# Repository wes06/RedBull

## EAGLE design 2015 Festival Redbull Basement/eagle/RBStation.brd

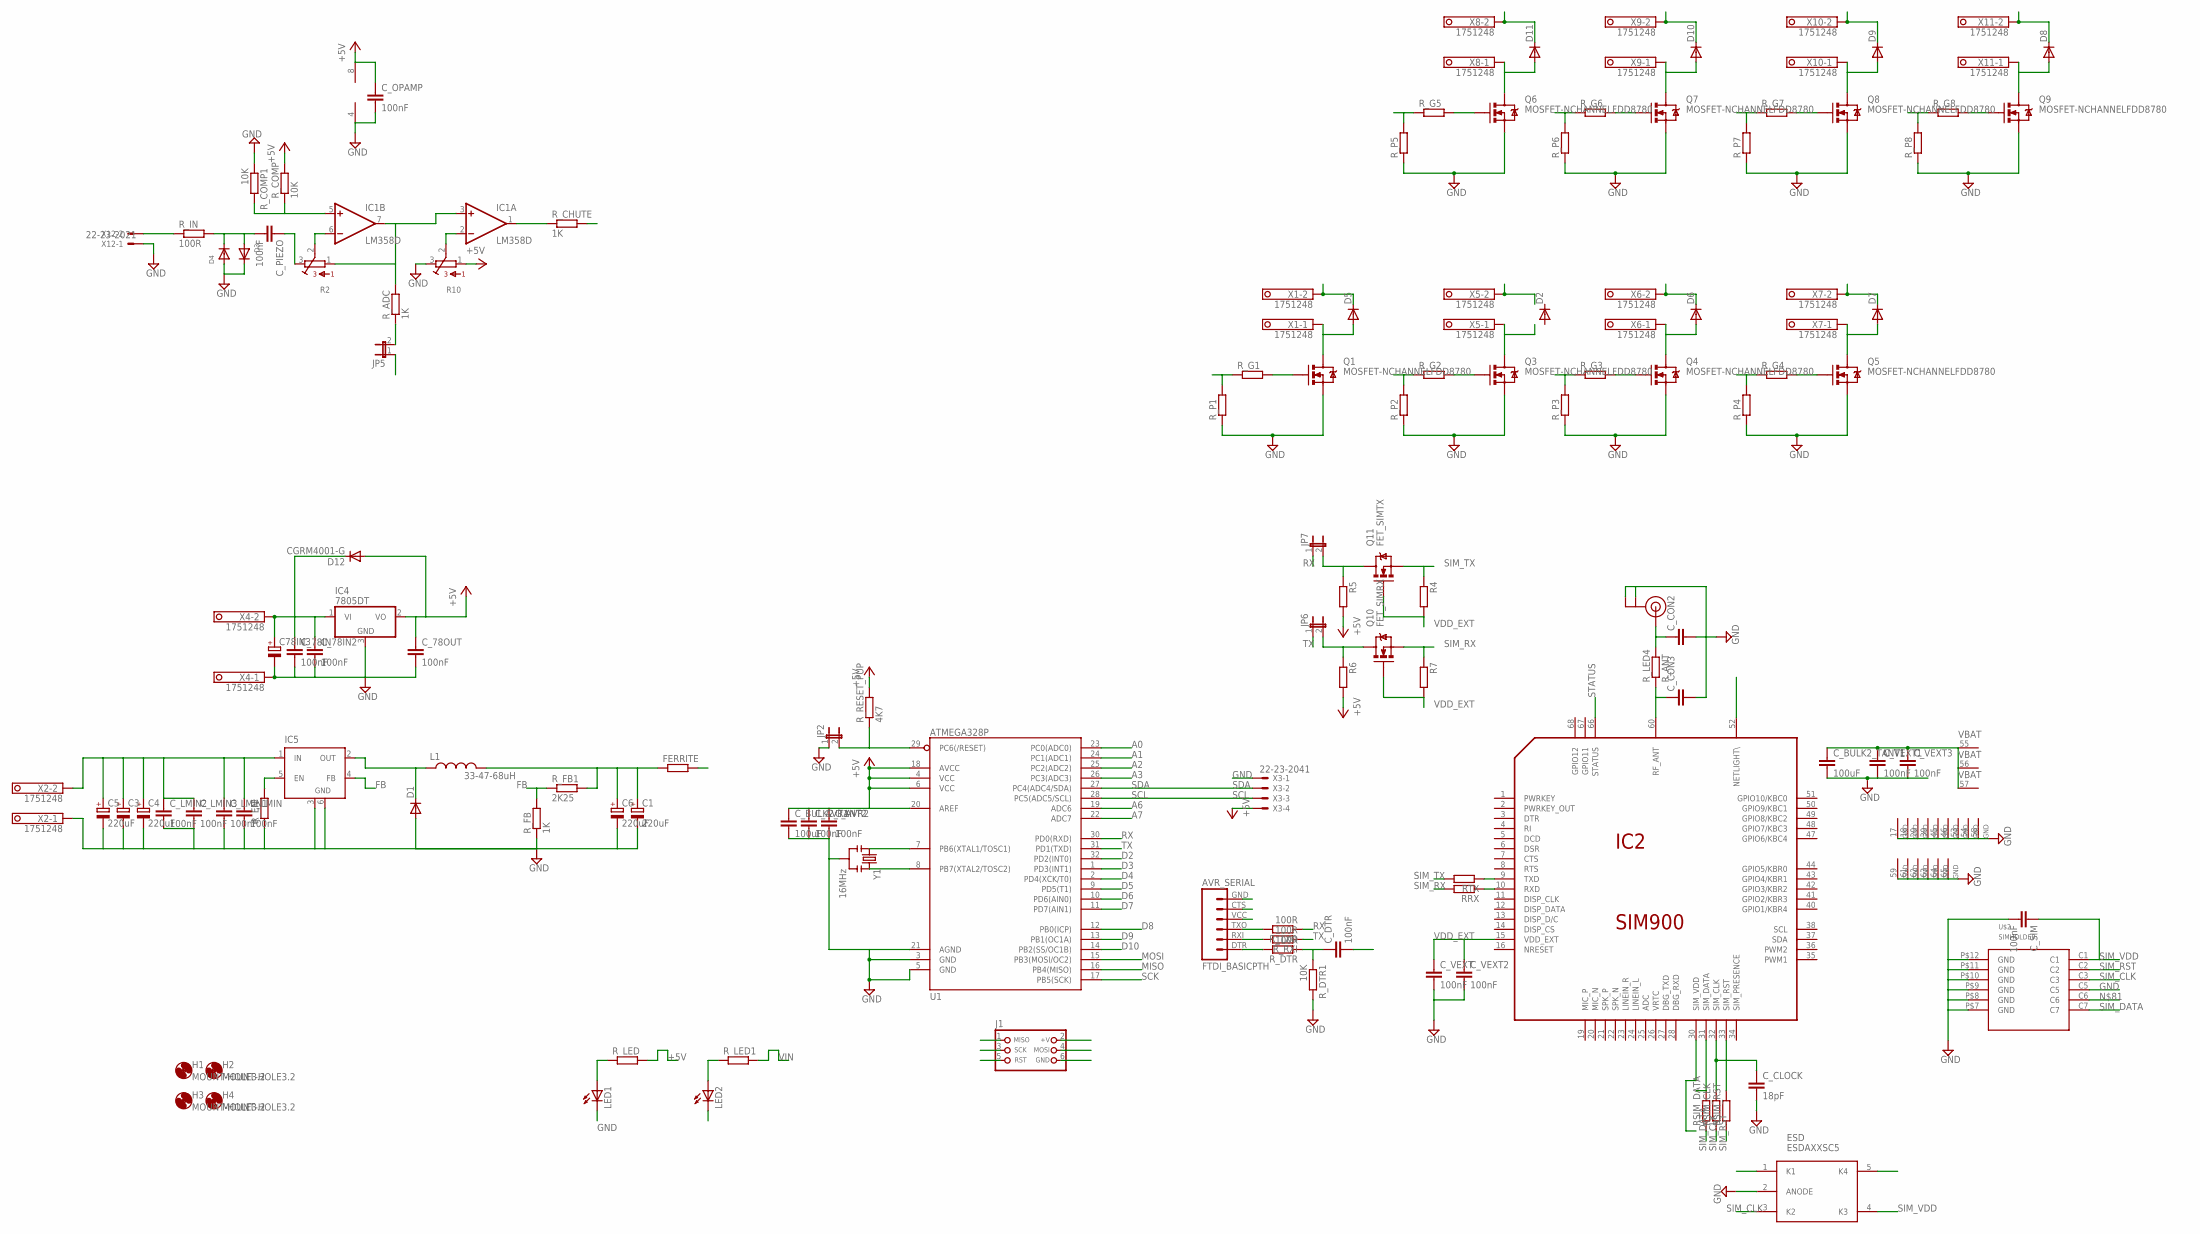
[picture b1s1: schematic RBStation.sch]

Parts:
AVR_SERIAL: FTDI_BASICPTH; FTDI_BASIC
C1, C4, C5, C6: 220uF; PANASONIC_F
C3, C78IN3: CPOL-EUF; PANASONIC_F
C_78IN, C_78IN2, C_78OUT: 100nF; C0805
C_AVR1: 100nF; C0805K
C_AVR2: 100nF; C0805
C_BULK2_TANT1, C_BULK2_TANT2: 100uF; C1210
C_CLOCK: 18pF; C0805
C_CON2, C_CON3: C-EUC0805; C0805
C_DTR: 100nF; C0805K
C_LMIN, C_LMIN1, C_LMIN2, C_LMIN3: 100nF; C0805
C_OPAMP: 100nF; C0805K
C_PIEZO: 100nF; C0805K
C_SIM: 100nF; C0805
C_VEXT, C_VEXT1, C_VEXT2: 100nF; C0805K
C_VEXT3: 100nF; C1210
D1: DIODESMB; SMB-DIODE
D2, D5, D6, D7, D8, D9, D10, D11: DIODESMA; SMA-DIODE
D3, D4: DIODESOD-123; SOD-123
D12: CGRM4001-G; SOD-123_MINI-SMA
ESD: ESDAXXSC5; SOT23-5
FERRITE: R-EU_R0805; R0805
H1, H2, H3, H4: MOUNT-HOLE3.2; 3,2
IC1: LM358D; SO08
IC2: SIM900
IC4: 7805DT; TO252
IC5: LM2596S; TO263-5
J1: CON_HEADER_PRG_AVR_ICSP; HEADER_PRG_2X03
JP2, JP5: JUMPER-2SMD-NC; SJ_2S
JP6, JP7: JUMPER-2PTH_LOCK; 1X02_LOCK
L1: 33-47-68uH; BOURNS-SRR1280
LED1, LED2: LEDCHIP-LED0805; CHIP-LED0805
Q1, Q3, Q4, Q5, Q6, Q7, Q8, Q9: MOSFET-NCHANNELFDD8780; DPAK
Q10: FET_SIMRX; SOT23
Q11: FET_SIMTX; SOT23
R2, R10: 3386-F; 3386F
R4, R5, R6, R7: R-EU_R0805; R0805
RRX: R-EU_M0805; M0805
RSIM_CLK: R-EU_M0805; M0805
RSIM_DATA: R-EU_M0805; M0805
RSIM_RST: R-EU_M0805; M0805
RTX: R-EU_M0805; M0805
R_ADC: 1K; M0805
R_CHUTE: 1K; M0805
R_COMP, R_COMP1: 10K; M0805
R_DTR: 100R; M0805
R_DTR1: 10K; M0805
R_EN: R-EU_M0805; M0805
R_FB: 1K; M0805
R_FB1: 2K25; M0805
R_G1, R_G2, R_G3, R_G4, R_G5, R_G6, R_G7, R_G8: R-EU_M0805; M0805
R_IN: 100R; M0805
R_LED, R_LED1: R-EU_M0805; M0805
R_LED4: R_ANT; R0805
R_P1, R_P2, R_P3, R_P4, R_P5, R_P6, R_P7, R_P8: R-EU_M0805; M0805
R_RESET_PUP: 4K7; M0805
R_RXI: 100R; M0805
R_TXO: 100R; M0805
U1: ATMEGA328P; TQFP32-08
U$1: U.FL
U$2: SIMHOLDER; WM9364CT-ND
X1, X2, X4, X5, X6, X7, X8, X9, X10, X11: 1751248
X3: 22-23-2041
X12: 22-23-2021
Y1: 16MHz; RESONATOR-SMD

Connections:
+5V: C_78OUT.1, C_AVR1.1, C_AVR2.1, C_BULK2_TANT2.1, C_OPAMP.1, D12.A, IC1.8 (V+), IC4.2 (VO), J1.2 (+V), R5.2, R6.2, R10.1, R_COMP.2, R_LED.2, R_RESET_PUP.2, U1.4 (VCC), U1.6 (VCC), U1.18 (AVCC), U1.20 (AREF), X3.4
A0: JP5.1, U1.23 (PC0(ADC0))
A1: U1.24 (PC1(ADC1))
A2: U1.25 (PC2(ADC2))
A3: U1.26 (PC3(ADC3))
A6: U1.19 (ADC6)
A7: U1.22 (ADC7)
C_CLK: C_CLOCK.1, IC2.32 (SIM_CLK), RSIM_CLK.2
D2: R_CHUTE.2, U1.32 (PD2(INT0))
D3: R_G1.1, R_P1.2, U1.1 (PD3(INT1))
D4: R_G2.1, R_P2.2, U1.2 (PD4(XCK/T0))
D5: R_G5.1, R_P5.2, U1.9 (PD5(T1))
D6: R_G6.1, R_P6.2, U1.10 (PD6(AIN0))
D7: R_G3.1, R_P3.2, U1.11 (PD7(AIN1))
D8: R_G4.1, R_P4.2, U1.12 (PB0(ICP))
D9: R_G7.1, R_P7.2, U1.13 (PB1(OC1A))
D10: R_G8.1, R_P8.2, U1.14 (PB2(SS/OC1B))
FB: IC5.4 (FB), R_FB.2, R_FB1.1
GND: AVR_SERIAL.GND (6), C1.-, C3.-, C4.-, C5.-, C6.-, C78IN3.-, C_78IN.2, C_78IN2.2, C_78OUT.2, C_AVR1.2, C_AVR2.2, C_BULK2_TANT1.2, C_BULK2_TANT2.2, C_CLOCK.2, C_CON2.2, C_CON3.2, C_LMIN.2, C_LMIN1.2, C_LMIN2.2, C_LMIN3.2, C_OPAMP.2, C_SIM.2, C_VEXT.2, C_VEXT1.2, C_VEXT2.2, C_VEXT3.2, D1.A, D3.C, D4.A, ESD.2 (ANODE), IC1.4 (V-), IC2.17 (GND), IC2.18 (GND), IC2.29 (GND), IC2.39 (GND), IC2.45 (GND), IC2.46 (GND), IC2.53 (GND), IC2.54 (GND), IC2.58 (GND), IC2.59 (GND), IC2.61 (GND), IC2.62 (GND), IC2.63 (GND), IC2.64 (GND), IC2.65 (GND), IC4.3 (GND), IC5.3 (GND), IC5.6 (GND), J1.6 (GND), JP2.1, LED1.C, LED2.C, Q1.3 (S), Q3.3 (S), Q4.3 (S), Q5.3 (S), Q6.3 (S), Q7.3 (S), Q8.3 (S), Q9.3 (S), R10.3, R_COMP1.1, R_DTR1.2, R_EN.1, R_FB.1, R_P1.1, R_P2.1, R_P3.1, R_P4.1, R_P5.1, R_P6.1, R_P7.1, R_P8.1, U1.3 (GND), U1.5 (GND), U1.21 (AGND), U$2.C5, U$2.P$7 (GND), U$2.P$8 (GND), U$2.P$9 (GND), U$2.P$10 (GND), U$2.P$11 (GND), U$2.P$12 (GND), X2.1, X3.1, X4.1, X12.1, Y1.2
MISO: J1.1 (MISO), U1.16 (PB4(MISO))
MOSI: J1.4 (MOSI), U1.15 (PB3(MOSI/OC2))
unnamed: Q1.1 (G), R_G1.2
unnamed: D1.C, IC5.2 (OUT), L1.P$2 (2)
unnamed: C_PIEZO.1, R2.3
unnamed: D5.A, Q1.4 (D), X1.1
unnamed: U1.7 (PB6(XTAL1/TOSC1)), Y1.1
unnamed: C_CON2.1, R_LED4.2, U$1.P$3 (SIGNAL)
unnamed: C_CON3.1, IC2.60 (RF_ANT), R_LED4.1
unnamed: IC2.31 (SIM_DATA), RSIM_DATA.2
unnamed: U$1.P$1 (GND), U$1.P$2 (GND)
unnamed: R_IN.1, X12.2
unnamed: U1.8 (PB7(XTAL2/TOSC2)), Y1.3
unnamed: IC2.33 (SIM_RST), RSIM_RST.2
unnamed: IC1.6 (-IN), R2.2
unnamed: JP5.2, R_ADC.1
unnamed: IC1.2 (-IN), R10.2
unnamed: C_BULK2_TANT1.1, C_VEXT1.1, C_VEXT3.1, FERRITE.2, IC2.55 (VBAT), IC2.56 (VBAT), IC2.57 (VBAT)
unnamed: LED2.A, R_LED1.1
unnamed: C_PIEZO.2, D3.A, D4.C, R_IN.2
unnamed: IC1.3 (+IN), IC1.7 (OUT), R2.1, R_ADC.2
unnamed: Q3.1 (G), R_G2.2
unnamed: Q3.4 (D), X5.1
unnamed: C_DTR.1, R_DTR.1, R_DTR1.1
unnamed: AVR_SERIAL.TXO (3), R_TXO.2
unnamed: AVR_SERIAL.RXI (2), R_RXI.2
unnamed: AVR_SERIAL.DTR (1), R_DTR.2
unnamed: Q4.1 (G), R_G3.2
unnamed: D6.A, Q4.4 (D), X6.1
unnamed: Q5.1 (G), R_G4.2
unnamed: LED1.A, R_LED.1
unnamed: D7.A, Q5.4 (D), X7.1
unnamed: Q6.1 (G), R_G5.2
unnamed: D11.A, Q6.4 (D), X8.1
unnamed: Q7.1 (G), R_G6.2
unnamed: D10.A, Q7.4 (D), X9.1
unnamed: Q8.1 (G), R_G7.2
unnamed: D9.A, Q8.4 (D), X10.1
unnamed: Q9.1 (G), R_G8.2
unnamed: D8.A, Q9.4 (D), X11.1
unnamed: IC2.9 (TXD), RTX.1
unnamed: IC2.10 (RXD), RRX.1
unnamed: JP7.2, Q11.3 (D), R5.1
unnamed: JP6.2, Q10.3 (D), R6.1
unnamed: C1.+, C6.+, FERRITE.1, L1.P$1 (1), R_FB1.2
unnamed: IC5.5 (EN), R_EN.2
unnamed: IC1.1 (OUT), R_CHUTE.1
NETLIGHT: IC2.52 (NETLIGHT\)
RESET: C_DTR.2, J1.5 (RST), JP2.2, R_RESET_PUP.1, U1.29 (PC6(/RESET))
ROITE: IC1.5 (+IN), R_COMP.1, R_COMP1.2
RX: JP7.1, R_TXO.1, U1.30 (PD0(RXD))
SCK: J1.3 (SCK), U1.17 (PB5(SCK))
SCL: U1.28 (PC5(ADC5/SCL)), X3.3
SDA: U1.27 (PC4(ADC4/SDA)), X3.2
SIM_CLK: ESD.3 (K2), RSIM_CLK.1, U$2.C3
SIM_DATA: ESD.1 (K1), RSIM_DATA.1, U$2.C7
SIM_RST: ESD.5 (K4), RSIM_RST.1, U$2.C2
SIM_RX: Q10.2 (S), R7.1, RRX.2
SIM_TX: Q11.2 (S), R4.1, RTX.2
SIM_VDD: C_SIM.1, ESD.4 (K3), IC2.30 (SIM_VDD), U$2.C1
STATUS: IC2.66 (STATUS)
TX: JP6.1, R_RXI.1, U1.31 (PD1(TXD))
VDD_EXT: C_VEXT.1, C_VEXT2.1, IC2.15 (VDD_EXT), Q10.1 (G), Q11.1 (G), R4.2, R7.2
VIN: C3.+, C4.+, C5.+, C_LMIN.1, C_LMIN1.1, C_LMIN2.1, C_LMIN3.1, D5.C, D6.C, D7.C, IC5.1 (IN), R_LED1.2, X1.2, X2.2, X5.2, X6.2, X7.2
VIN2: C78IN3.+, C_78IN.1, C_78IN2.1, D8.C, D9.C, D10.C, D11.C, D12.C, IC4.1 (VI), X4.2, X8.2, X9.2, X10.2, X11.2

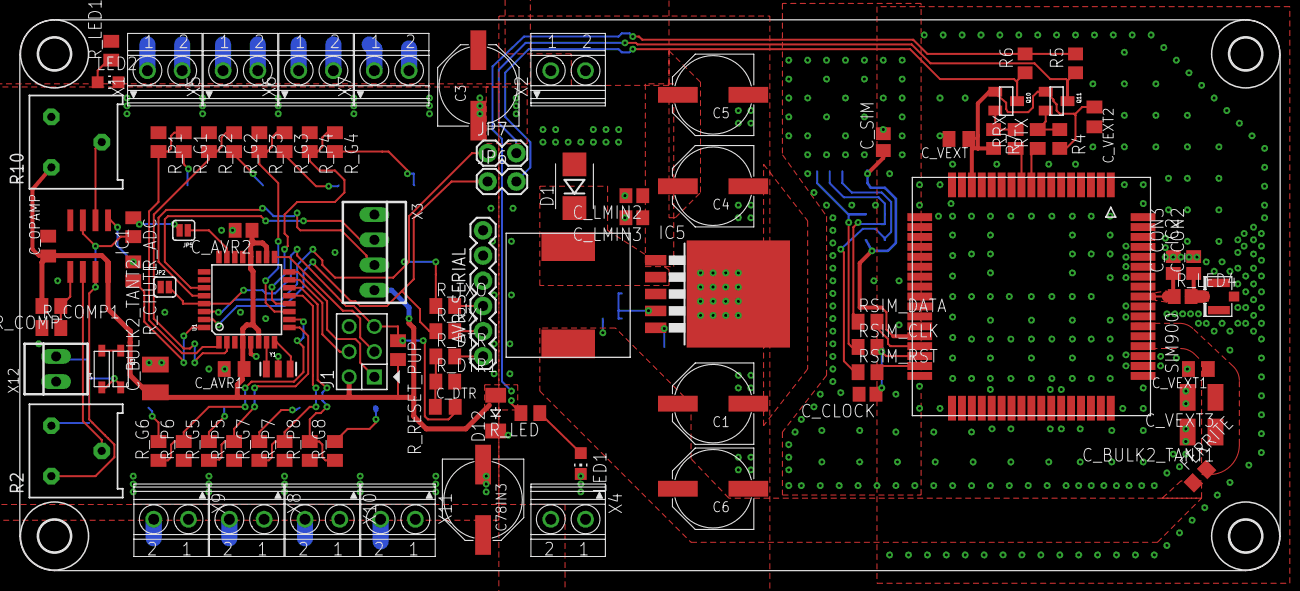
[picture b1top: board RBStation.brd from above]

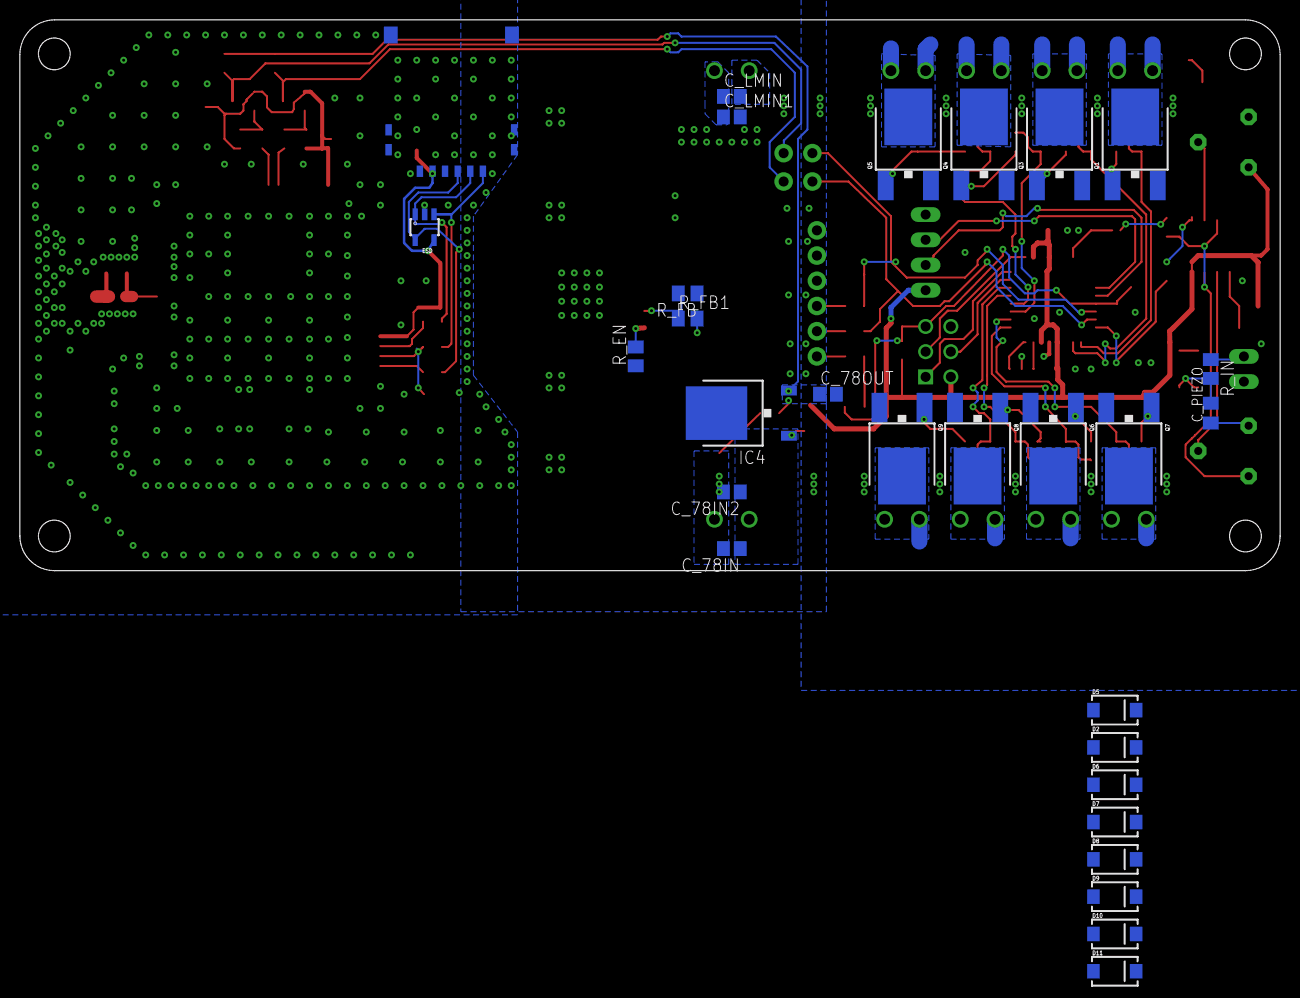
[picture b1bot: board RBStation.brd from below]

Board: 2 copper layers, 127.0 x 55.5 mm, 128 parts (29 on the bottom side), 77 nets.

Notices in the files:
parts and their libraries:
SparkFun-DigitalIC: Licensing: CC v3.0 Share-Alike You are welcome to use this library for commercial purposes.
